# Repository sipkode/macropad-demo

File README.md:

# macropad-demo
Following the PCB design tutorial from AI03

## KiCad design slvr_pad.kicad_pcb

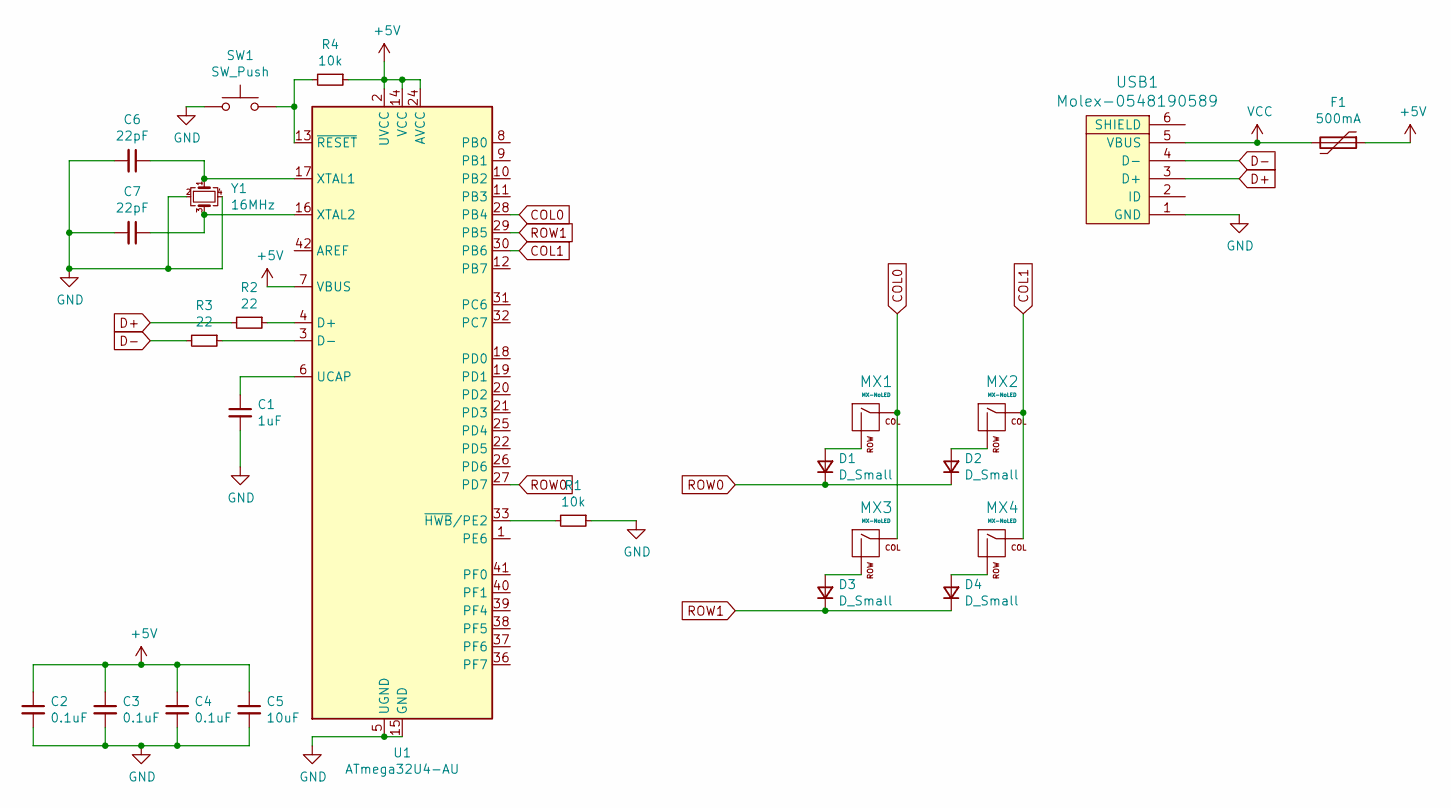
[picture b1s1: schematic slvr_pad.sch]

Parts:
C1: 1uF; C_0805_2012Metric
C2, C3, C4: 0.1uF; C_0805_2012Metric
C5: 10uF; C_0805_2012Metric
C6, C7: 22pF; C_0805_2012Metric
D1, D2, D3, D4: D_Small; D_SOD-123
F1: 500mA; Fuse_1206_3216Metric
MX1, MX2, MX3, MX4: MX-NoLED; MX-1U-NoLED
R1, R4: 10k; R_0805_2012Metric
R2, R3: 22; R_0805_2012Metric
SW1: SW_Push; SKQG-1155865
U1: ATmega32U4-AU; TQFP-44_10x10mm_P0.8mm
USB1: Molex-0548190589
Y1: 16MHz; Crystal_SMD_3225-4Pin_3.2x2.5mm

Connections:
+5V: C2.1, C3.1, C4.1, C5.1, F1.1, R4.1, U1.2 (UVCC), U1.7 (VBUS), U1.14 (VCC), U1.24 (AVCC), U1.34 (VCC), U1.44 (AVCC)
COL0: MX1.1 (COL), MX3.1 (COL), U1.28 (PB4)
COL1: MX2.1 (COL), MX4.1 (COL), U1.30 (PB6)
D+: R2.2, USB1.3 (D+)
D-: R3.2, USB1.4 (D-)
GND: C1.2, C2.2, C3.2, C4.2, C5.2, C6.2, C7.2, R1.1, SW1.1, U1.5 (UGND), U1.15 (GND), U1.23 (GND), U1.35 (GND), U1.43 (GND), USB1.1 (GND), Y1.2, Y1.4
unnamed: C1.1, U1.6 (UCAP)
unnamed: C6.1, U1.17 (XTAL1), Y1.1
unnamed: C7.1, U1.16 (XTAL2), Y1.3
unnamed: D1.2 (A), MX1.2 (ROW)
unnamed: D2.2 (A), MX2.2 (ROW)
unnamed: D3.2 (A), MX3.2 (ROW)
unnamed: D4.2 (A), MX4.2 (ROW)
unnamed: R1.2, U1.33 (~HWB~/PE2)
unnamed: R2.1, U1.4 (D+)
unnamed: R3.1, U1.3 (D-)
unnamed: R4.2, SW1.2, U1.13 (~RESET)
ROW0: D1.1 (K), D2.1 (K), U1.27 (PD7)
ROW1: D3.1 (K), D4.1 (K), U1.29 (PB5)
VCC: F1.2, USB1.5 (VBUS)

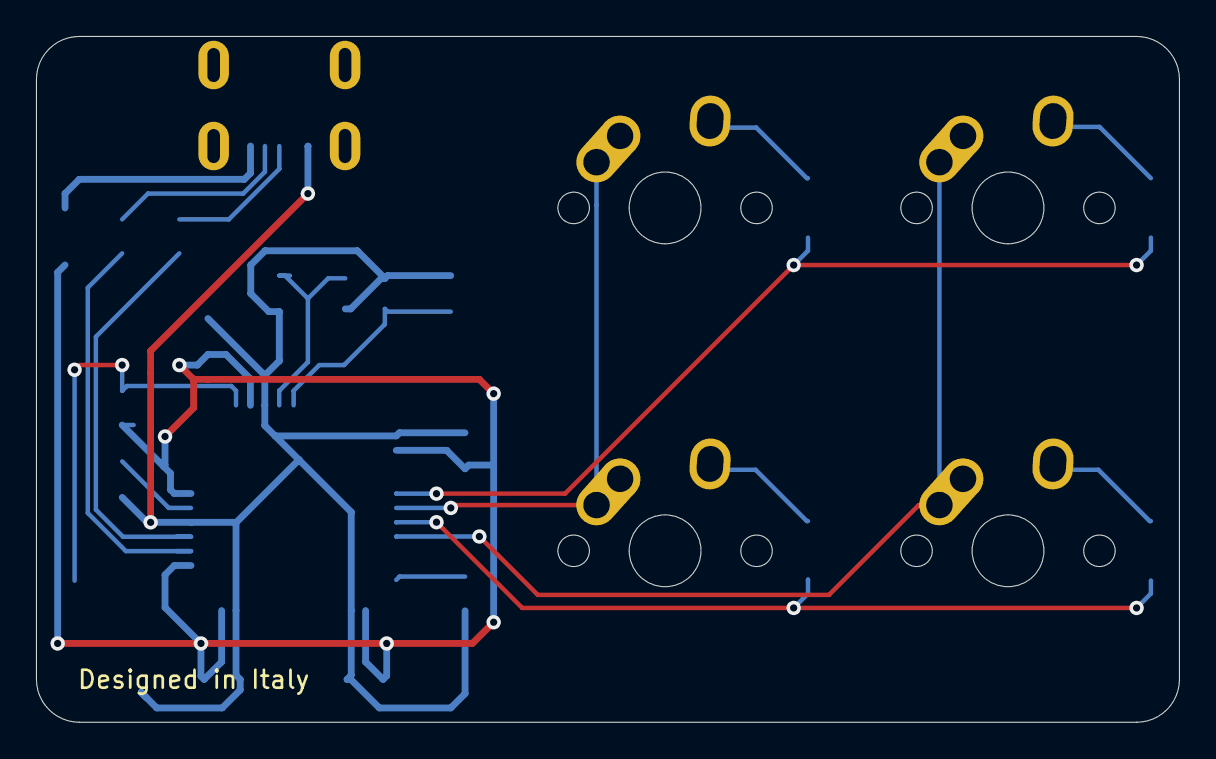
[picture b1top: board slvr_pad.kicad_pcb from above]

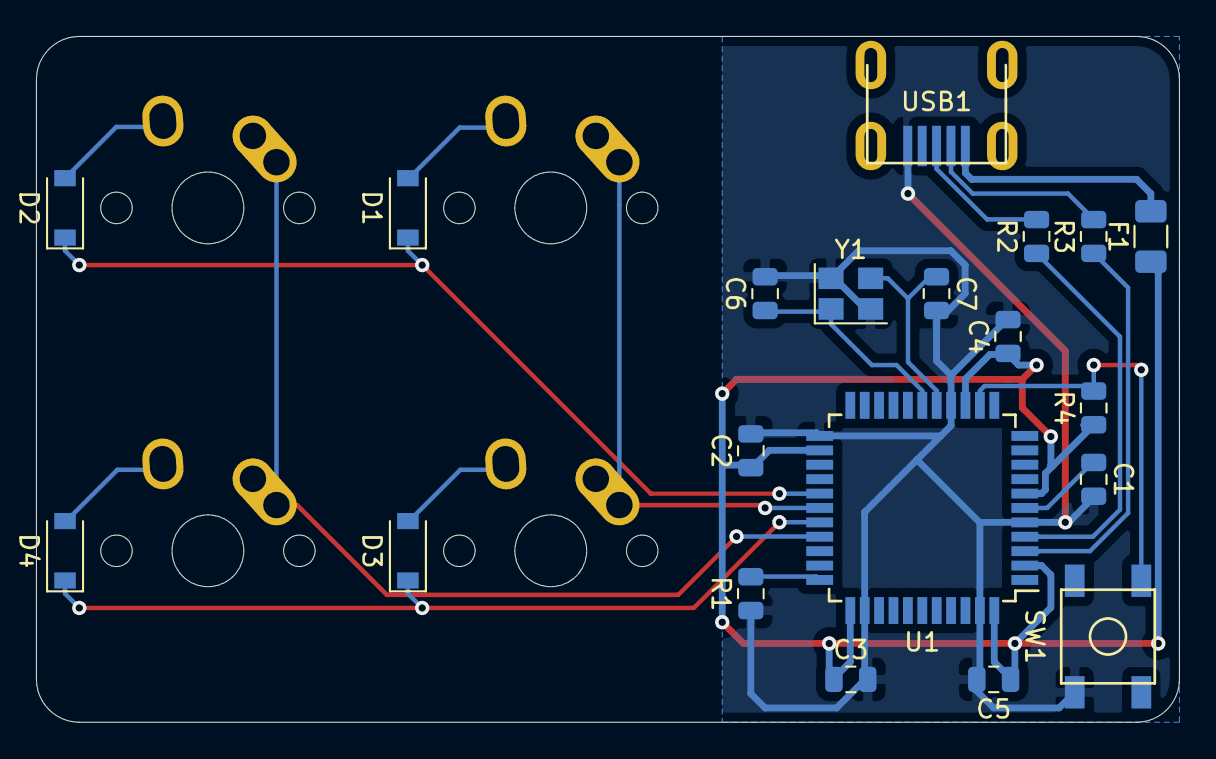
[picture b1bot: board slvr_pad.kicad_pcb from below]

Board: 2 copper layers, 63.5 x 38.1 mm, 24 parts (20 on the bottom side), 20 nets.

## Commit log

2020-07-04 First: Commit empty KiCAD project files
2020-07-04 Deps: Add ai03 submodules
2020-07-04 Deps: Add ai03 libraries to KiCad
2020-07-04 SCH: Add atmega MCU section
2020-07-05 SCH: Add switch matrix and component footprints.
2020-07-05 PCB: Components placed
2020-07-06 PCB: Route all traces
2020-07-06 PCB: Add ground fill
2020-07-09 PCB: Add 3D components and fix warnings
